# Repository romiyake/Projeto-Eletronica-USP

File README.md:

# Projeto Fonte Reguladora de Tensão
Objetivo do projeto é criar um fonte reguladora de tensão para a matéria [SSC0180 - Eletrônica para Computação](https://gitlab.com/simoesusp/disciplinas/-/tree/master/SSC0180-Eletronica-para-Computacao) da Universidade de São Paulo campus de São Carlos.
## Especificação
Fonte reguladora de tensão ajustável, que receba 127V de valor eficáz e consiga emitir entre 12V-3V e uma corrente de 100mA.
## Lista de componentes
| Quantidade      | Componente       | Preço  |
| :-------------: |:-------------:| -----:|
| 1 | LED Difuso 5mm Vermelho | [R$0,23](https://www.baudaeletronica.com.br/led-difuso-5mm-vermelho.html) |
| 1 | Transistor NPN BC337 | [R$0,20](https://www.baudaeletronica.com.br/transistor-npn-bc337.html) |
| 1 | Transformador Trafo 7,5V + 7,5V 200mA | [R$21,83](https://www.baudaeletronica.com.br/transformador-trafo-7-5v-7-5v-200ma-110-220vac.html) |
| 4 | Diodo 1N4007 | [4 x R$0,09](https://www.baudaeletronica.com.br/diodo-1n4007.html) |
| 2 | Resistor 1k2 1/4W | [2 x R$0,05](https://www.baudaeletronica.com.br/resistor-1k2-5-1-4w.html) |
| 1 | Resistor 5k6 1/4W | [R$0,05](https://www.baudaeletronica.com.br/resistor-5k6-5-1-4w.html) |
| 1 | Diodo Zener BZX55C | [R$0,08](https://www.baudaeletronica.com.br/diodo-zener-bzx55c-13v-0-5w.html) |
| 1 | Potenciômetro Linear de 10k | [R$1,61](https://www.baudaeletronica.com.br/potenciometro-linear-de-10k-10000.html) |
| 1 | Capacitor 560µ 35V | [R$2,90](https://shopee.com.br/CAPACITOR-ELETROL%C3%8DTICO-RADIAL-560uF-35V-105-%C2%B0C-KIT-3p%C3%A7s-i.341792361.9902590827) |
| Total | | R$27,36 |
## Simulação do circuito

[O circuito pode ser acessado clicando aqui](https://tinyurl.com/yf9bfx3d "Falstad")
## Esquemático no Eagle

[.sch pode ser acessado clicando aqui](https://github.com/romiyake/Projeto-Eletronica-USP/blob/main/Eagle/Fonte.sch)
## PCB no Eagle

[.brd pode ser acessado clicando aqui](https://github.com/romiyake/Projeto-Eletronica-USP/blob/main/Eagle/Fonte.brd)
## Vídeo explicativo
[Vídeo no youtube explicando a escolha de cada componente](https://youtu.be/Pa7L1ARfAt0)

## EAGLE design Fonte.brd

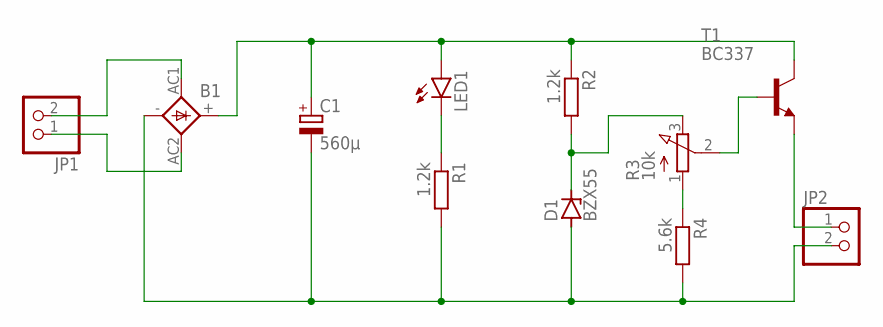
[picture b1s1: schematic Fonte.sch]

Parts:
B1: 2KBB-R
C1: 560µ; E3,5-10
D1: BZX55; DO35Z10
JP1, JP2: PINHD-1X2; 1X02
LED1: LED5MM
R1, R2: 1.2k; 0204/7
R3: 10k; 3RP/1610N
R4: 5.6k; 0204/7
T1: BC337; TO92

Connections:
unnamed: B1.AC1, JP1.2
unnamed: B1.AC2, JP1.1
unnamed: D1.C, R2.2, R3.3 (E)
unnamed: B1.-, C1.-, D1.A, JP2.2, R1.2, R4.2
unnamed: R3.1 (A), R4.1
unnamed: B1.+, C1.+, LED1.A, R2.1, T1.3 (C)
unnamed: LED1.K (C), R1.1
unnamed: R3.2 (S), T1.2 (B)
unnamed: JP2.1, T1.1 (E)

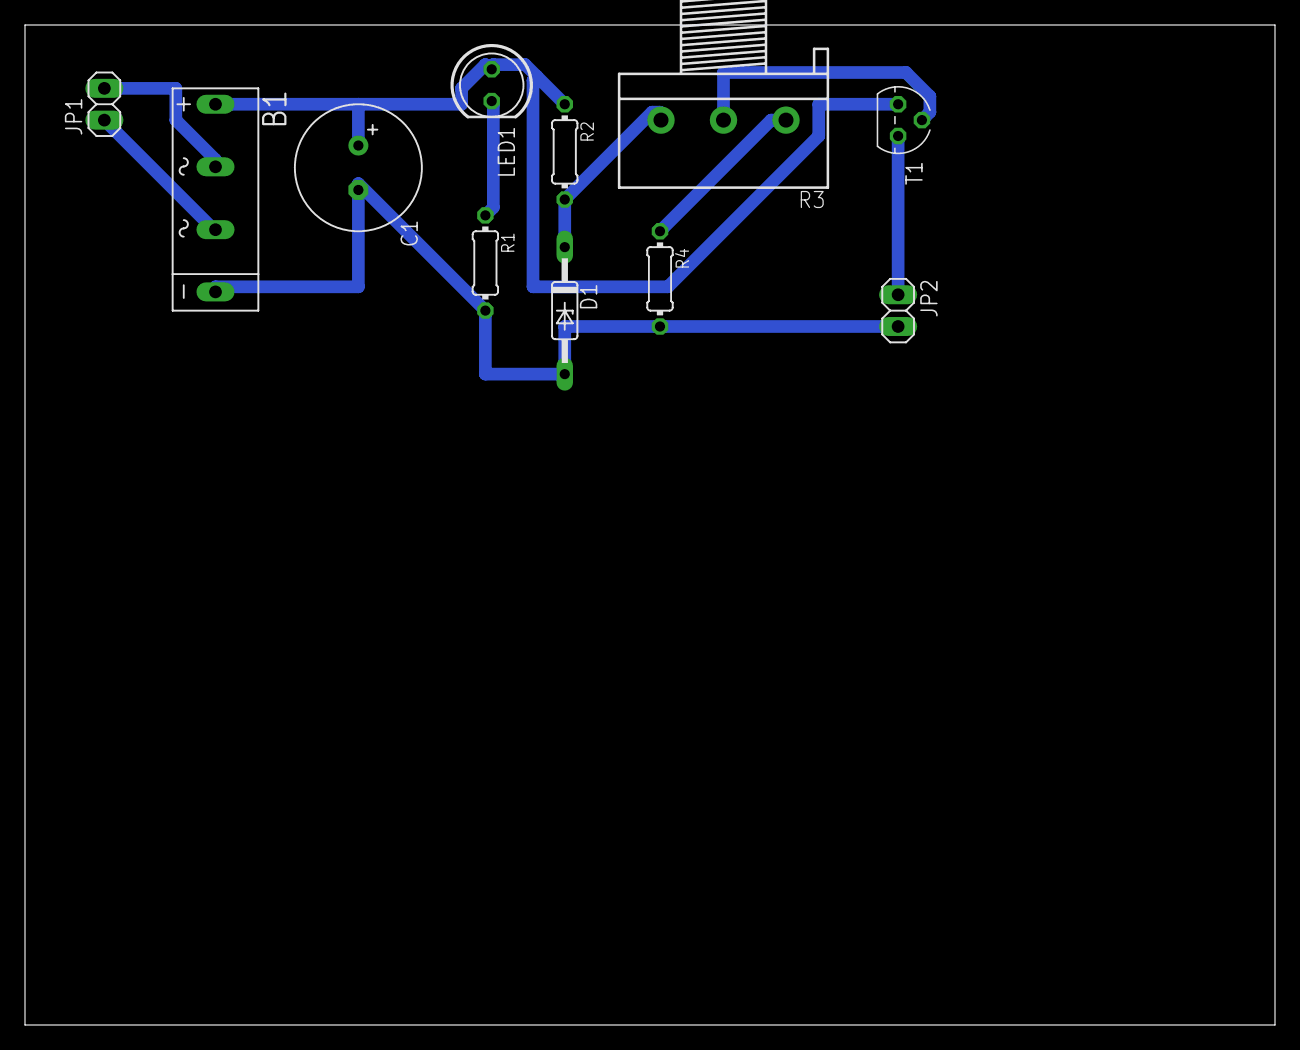
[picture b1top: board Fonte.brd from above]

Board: 2 copper layers, 100.0 x 80.0 mm, 11 parts (0 on the bottom side), 9 nets.
